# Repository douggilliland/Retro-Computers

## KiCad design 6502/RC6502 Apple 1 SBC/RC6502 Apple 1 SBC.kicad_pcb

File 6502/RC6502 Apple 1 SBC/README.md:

# RC6502 Apple 1 SBC

Did you ever wonder what the first computer created by Apple was like, and then checked what getting one might cost? Well, only a few were made and those that still exist probably would cost you more than my car! Steve Wozniak built what would later be called the Apple I computer in his garage, using only common over the counter components the result was an interesting computer that still holds the imagination of many computer geeks to this day. I don't own a garage so I was limited by whatever I could do from the confines of my kitchen table, the RC6502 was what I came up with and with the files freely available on GitHub you can too!

There are two versions of the RC6502, one has a card for every basic function such as CPU, RAM (redesigned version of also supports ROM), separate ROM as well as a serial card that replaces the traditional CRT and ASCII keyboard with an Arduino Nano. Doing it this way requires a backplane to connect everything together, this may be the version to build either because you want to study each of them in detail to figure out their secrets or simply because you want the option to easily replace them. The other one, this one actually, is the SBC-version (Single Board Computer) - this is the version to get if you want to learn a bit about the computer and enjoy building kits that are in a more compact form factor. It looks nice on shelf, or in a small drawer (if you don't get a vote on what belongs on display in your home). Most can be accomplished with the SBC version, so for your first build I recommend that you start with the SBC ([order](https://www.pcbway.com/project/shareproject/RC6502_Apple_1_SBC__revision_D_.html?inviteid=88707)) as well as a backplane ([order](https://www.pcbway.com/project/shareproject/RC6502_Apple_1_Replica__Backplane_module_revision_A_.html?inviteid=88707)) (so you can create and add features later).

Excited yet? Ofcourse you are, the next step is getting a PCB made and with the files available here you can have a company such as [PCBWay](https://www.pcbway.com/project/shareproject/RC6502_Apple_1_SBC__revision_D_.html?inviteid=88707) make a stack of them for around 5$, then have a look through the BOM (Bill Of Manufacturing) below to figure out what kind of components you'd need later to put it all together. Other than that you need basic tools such as a good soldering iron with a small-ish tip, lead-based solder with a resin core is recommended for beginners and then finally you'll need a basic EEPROM programmer (I use a cheap, but fantastic one called MiniPro TL866A).

The project uses only through-hole components that are easy for beginners, these have a set of pins or wires that are threaded through the holes of the PCB and then soldered on to the backside of the PCB. You can assemble it in the order of your own choosing as long as everything goes in the right place, but here are some hints to get started: do smaller parts such as the resistors first, then followed by the capacitors, IC sockets and then finally the larger components. By doing it this way, we're gradually going from the components closest to the board and successively moving onto taller components - this makes it easier to keep everything flush with the board. The components icons on the top of the PCB, what we hardware geeks usually refer to as the silkscreen, shows you which components goes where - take care that they are oriented the correct way, where it matters it'll be marked. Sockets will have a little indent marked on it similar to what you find on the PCB, for the electrolytic capacitors (round towers) you'll be able to match a stripe on one of the sides to the filled half of the symbol (this is the minus side).

Take it slow and steady, enjoy the feeling of building a computer by hand. Study the text on the backside of the PCB as you go along, it'll have some text on it describing what most of the components you are installing actually does! If afterwards you want to study everything in detail, you can do so by studying the schematic for the whole thing at your leasure. Having problems with it? Now, I'm afraid you no longer have the option to avoid the schematic, but happily most problems can be fixed by verifying each connection by using a cheap multimeter set to continuity mode. If you print the schematic, you can mark everything you've checked with a pen so you won't overlook anything - this is where you'll be learning the most! Sometimes the wrong things have been accidentally connected, usually by a stray splash of solder - these are quickly found using the same continuity check, systematically work through each of the ICs to see if pins next to each other have been connected without a corresponding link on the schematic. Don't feel bad that everything didn't work from the get go, that just means you got some extra opportunities to learn even more than expected!

The original computer had circuits for displaying data on a screen and reading input via a physical keyboard, but to keep things simple we are instead using an Arduino Nano to replace these parts - that way, you thanfully don't need to buy an antique keyboard or a scary CRT monitor in order to use it! You can communicate with the computer you built using a terminal emulator program such as PuTTy, SecureCRT or similar over the serial interface provided by the Arduino Nano. The Nano of course also need some software running on it, you'll find that in the form of an Arduino sketch called "[PIA Communicator](https://github.com/tebl/RC6502/tree/master/RC6502%20Serial%20IO/pia_communicator)", for more information see the details for the standalone [Serial IO](https://github.com/tebl/RC6502-Apple-1-Replica/tree/master/RC6502%20Serial%20IO)-module. 

The firmware that goes into the EEPROM hasn't been changed since Wozniak himself wrote it, but as long as you have the programmer handy you can easily flash it into place using the software that came with the programmer (MiniPro Programmer, if you bought the one I'm using). Today the [8 KB binary file](https://github.com/tebl/RC6502/tree/master/RC6502%20ROM/firmware) will seem really small, but even still it contains everything you'll need to get started and even a lot more. You've got a complete version of Basic environment in there, but since it's an Apple 1 the first thing you'll see is something called a computer monitor - WozMon! The monitor allows you to interact with the system by peeking and poking memory locations to your hearts content!

At this point you'll certainly have learned a lot, after all you've actually built an entire computer! Thankfully you had some modern tools available, but please take a moment to contemplate the genious needed to build this thing back in 1976! Still wanting more, why not try your hand at designing some extra modules to use with that backplane connector? Add a parallell port, replace the display portion with a proper LCD, or you could even go as far as adding a few pretty blinking lights - the possibilities are truly endless (so long as it's within 64K)!

## Errata
Revisions D and E of the SBC was missing a line powering the CPU, this is fixed by adding a piece of patch wire or simply a piece of resistor leftovers. Refer to the image below to see where it should be added, but leave some room so that it doesn't short to the pads now in the middle of the wire.

# Schematic
The supplied KiCad files should be sufficient as both a schematic and as a starting point for ordering PCBs (basically you could just zip the contents of the export folder and upload that on a fabrication site), the schematic is also available in [PDF-format](https://github.com/tebl/RC6502/raw/master/RC6502%20Apple%201%20SBC/export/RC6502%20Apple%201%20SBC.pdf) so that you can refer to it while troubleshooting. You could even print it out and hang it on your office wall, excellent conversation starter at any technology-oriented business worth working at!

# BOM
This is the part list as it stands now, most should be easy to get a hold of from your local electronic component shop though you might have to consider other sources for the older parts such as CPU, memory and PIA. Personally I bought most components with free shipping from China via AliExpress, prices will vary though you should be able to find most components in larger quantities than you'll ever need for the cost of a few cups of fancy coffee! You don't even need the newest and fastest components, after all it's going into a 70s-era computer so don't go overboard unless you absolutely want to (you can replace 74LS ICs with 74HCT or 74ALS if you want something newer). Most components have been produced by various manufacturers, these mostly do the same thing without any relevant differences though the choice of CPU and PIA could lead to incompatibilities so I've specified the ones I've had success with (probably also the cheapest ones available).

Some vendors will have the same ICs in different form factors, the ones you want will often be specified as being in the form of a DIP/PDIP package. Usually you'll want sockets for each of the ICs as well, a bag of assorted sockets should be easily available without setting you back more than a couple bucks. With the sockets in place, you don't need to dread having to remove an IC later, this leads to easier fault finding and you can easily "borrow"  them for other projects later! For the pin headers, both male and female - if you can't find the exact pin count, just buy the longer versions and snip off the parts you don't need. Electrolytic capacitors have a max voltage rating, the cheapest are 16V and should be more than enough - you can use higher rated components if you want to, but note that these might be slightly bigger thought you'll probably be able to fit in there anyway. Personally I prefer the look of the monolithic capacitors over the regular ceramic ones, but either is fine!

| Reference    | Item                                  | Count |
| ------------ | ------------------------------------- | ----- |
| PCB          | Fabricate yourself using Gerber files ([order](https://www.pcbway.com/project/shareproject/RC6502_Apple_1_SBC__revision_D_.html?inviteid=88707)) |     1 |
| U1           | 6502 CPU DIP-40, UM6502 or SY6502     |     1 |
| U2           | 62256 Static RAM DIP-28               |     1 |
| U3           | 74LS138 DIP                           |     1 |
| U4           | 28C64 or 28C256 DIP-28, EEPROM        |     1 |
| U5           | 74LS00 DIP                            |     1 |
| U6           | NE555 DIP                             |     1 |
| U7           | 74LS04 DIP                            |     1 |
| U8           | MC6821P PIA DIP-40                    |     1 |
| U9           | MCP23S17 DIP-28                       |     1 |
| X1           | 1.000Mhz TTL Oscillator, (DIP 14)     |     1 |
| R1,R6-R8,R10 | 3k3 (3300) ohm resistor               |     5 |
| R2           | 1M ohm resistor                       |     1 |
| R3           | 47k ohm resistor                      |     1 |
| R4           | 1k ohm resistor                       |     1 |
| R5           | 330 ohm resistor                      |     1 |
| R9           | 10k ohm resistor                      |     1 |
| D1           | 5mm LED diode, green or red color     |     1 |
| J1, J8       | Single row, 2p right angle connector  |     2 |
| J2           | 15p female pin headers                |     2 |
| J3           | Single row, 39p right angle connector |     1 |
| J4-J7        | Not needed, holes included with PCB   |     4 |
| J9, J10      | Single row, 3p right angle connector  |     2 |
| C1-C9, C11   | 100nF ceramic capacitor               |    10 |
| C10          | 10uF 16V electrolytic capacitor       |     1 |
| C12          | 10nF ceramic capacitor                |     1 |
| SW1          | Momentary push button                 |     1 |
|              | Jumpers for settings (CAP headers)    |     5 |
| Nano         | Arduino Nano v3.0 with USB cable      |     1 |

If you would like to have a copy of one or more modules, what you'll need to do is zip up the contents of the export directory for each module and give that to your favourite PCB fabrication plant. Personally I prefer to use [PCBWay](https://www.pcbway.com/setinvite.aspx?inviteid=88707), each module is only 5$ each and new accounts even get the first one free! Please use the supplied link when signing up to help me support this project, I'll get a small discount on future orders and hopefully I can afford to keep developing new and exciting modules. Some of the modules also have an order-link, using this you won't have to deal with the rather daunting PCB fabrication order forms so you know it'll work on the first order attempt!

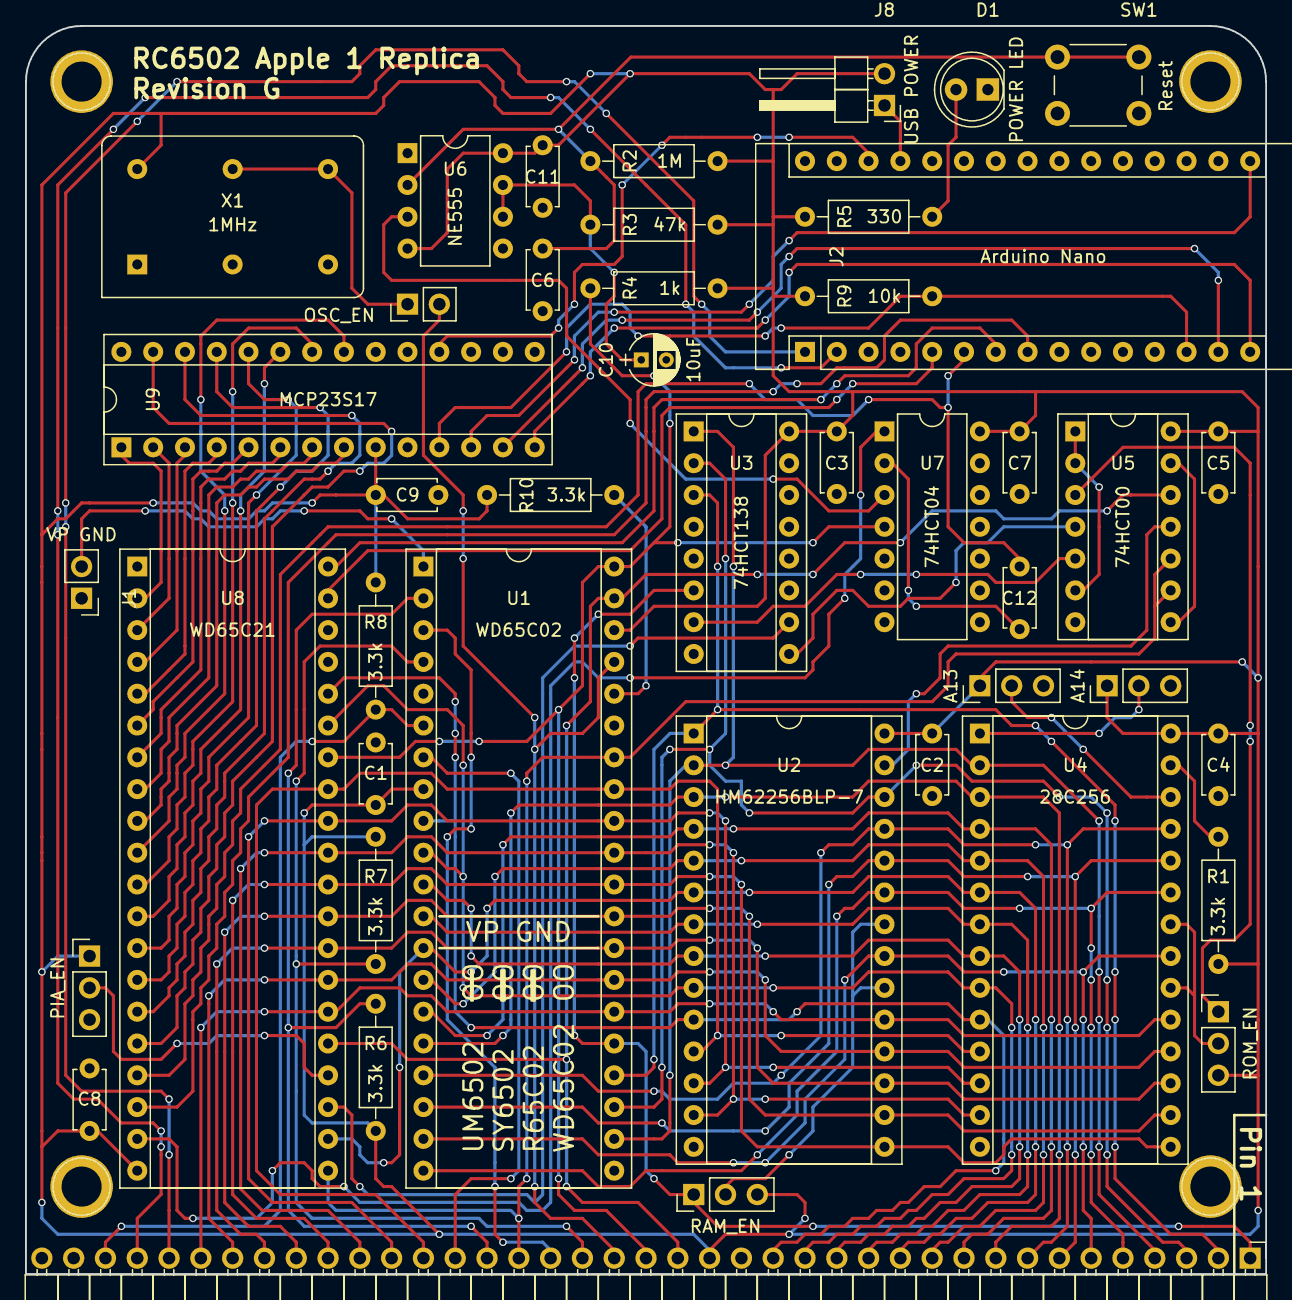
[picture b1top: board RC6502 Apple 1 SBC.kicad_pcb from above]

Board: 2 copper layers, 99.1 x 99.7 mm, 48 parts (0 on the bottom side), 84 nets.

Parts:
A13: A13 Select; Pin_Header_Straight_1x03_Pitch2.54mm
A14: A14 Select; Pin_Header_Straight_1x03_Pitch2.54mm
C1, C2, C3, C4, C5, C6, C7, C8, C9, C11: 100nF; C_Disc_D4.7mm_W2.5mm_P5.00mm
C10: 10uF; CP_Radial_D4.0mm_P2.00mm
C12: 10nF; C_Disc_D4.7mm_W2.5mm_P5.00mm
D1: Power; LED_D5.0mm
J1: VP GND; Pin_Header_Straight_1x02_Pitch2.54mm
J2: Arduino Nano; Arduino_Nano
J3: Backplane; Pin_Header_Angled_1x39_Pitch2.54mm
J4, J5, J6, J7: Hole; Mounting
J8: Power; Pin_Header_Angled_1x02_Pitch2.54mm
J9: ROM_EN; Pin_Header_Straight_1x03_Pitch2.54mm
J10: RAM_EN; Pin_Header_Straight_1x03_Pitch2.54mm
J11: PIA_EN; Pin_Header_Straight_1x03_Pitch2.54mm
JP1: OSC_EN; Pin_Header_Straight_1x02_Pitch2.54mm
R1, R6, R7, R8, R10: 3.3k; R_Axial_DIN0207_L6.3mm_D2.5mm_P10.16mm_Horizontal
R2: 1M; R_Axial_DIN0207_L6.3mm_D2.5mm_P10.16mm_Horizontal
R3: 47k; R_Axial_DIN0207_L6.3mm_D2.5mm_P10.16mm_Horizontal
R4: 1k; R_Axial_DIN0207_L6.3mm_D2.5mm_P10.16mm_Horizontal
R5: 330; R_Axial_DIN0207_L6.3mm_D2.5mm_P10.16mm_Horizontal
R9: 10k; R_Axial_DIN0207_L6.3mm_D2.5mm_P10.16mm_Horizontal
SW1: RESET; SW_PUSH_6mm
U1: WD65C02; DIP-40_W15.24mm_Socket
U2: HM62256BLP-7; DIP-28_W15.24mm_Socket
U3: 74HCT138; DIP-16_W7.62mm_Socket
U4: 28C256; DIP-28_W15.24mm_Socket
U5: 74HCT00; DIP-14_W7.62mm_Socket
U6: NE555; DIP-8_W7.62mm
U7: 74HCT04; DIP-14_W7.62mm
U8: WD65C21; DIP-40_W15.24mm_Socket
U9: MCP23S17; DIP-28_W7.62mm_Socket
X1: 1MHz; Oscillator_DIP-14

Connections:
A0: J3.16, U1.9, U2.10, U4.10, U8.36
A1: J3.15, U1.10, U2.9, U4.9, U8.35
A2: J3.14, U1.11, U2.8, U4.8
A3: J3.13, U1.12, U2.7, U4.7
A4: J3.12, U1.13, U2.6, U4.6, U8.22
A5: J3.11, U1.14, U2.5, U4.5
A6: J3.10, U1.15, U2.4, U4.4
A7: J3.9, U1.16, U2.3, U4.3
A8: J3.8, U1.17, U2.25, U4.25
A9: J3.7, U1.18, U2.24, U4.24
A10: J3.6, U1.19, U2.21, U4.21
A11: J3.5, U1.20, U2.23, U4.23
A12: J3.4, U1.22, U2.2, U3.1, U4.2
A13: J3.3, U1.23, U2.26, U3.2
A13_W: A13.2, U4.26
A14: J3.2, U1.24, U2.1, U3.3
A14_W: A14.2, U4.1
A15: J3.1, J10.1, U1.25, U3.6
CLOCK: J3.21, JP1.2, U1.37
CS_PIA: U3.10, U8.23
CS_ROM: J9.1, U5.3
D0: J3.27, U1.33, U2.11, U4.11, U8.33
D1: J3.28, U1.32, U2.12, U4.12, U8.32
D2: J3.29, U1.31, U2.13, U4.13, U8.31
D3: J3.30, U1.30, U2.15, U4.15, U8.30
D4: J3.31, U1.29, U2.16, U4.16, U8.29
D5: J3.32, U1.28, U2.17, U4.17, U8.28
D6: J3.33, U1.27, U2.18, U4.18, U8.27
D7: J3.34, U1.26, U2.19, U4.19, U8.26
GND: A13.3, A14.3, C1.2, C2.2, C3.2, C4.2, C5.2, C6.2, C7.2, C8.2, C9.2, C10.2, C11.2, D1.1, J1.1, J2.29, J3.17, J11.3, SW1.1, U1.21, U2.14, U3.4, U3.5, U3.8, U4.14, U5.7, U6.1, U7.5, U7.7, U7.9, U7.11, U7.13, U8.1, U9.10, U9.15, U9.16, U9.17, X1.7
IRQ: J3.22, R7.1, U1.4
KBD_D0: U8.2, U9.1
KBD_D1: U8.3, U9.2
KBD_D2: U8.4, U9.3
KBD_D3: U8.5, U9.4
KBD_D4: U8.6, U9.5
KBD_D5: U8.7, U9.6
KBD_D6: U8.8, U9.7
KBD_D7: U8.9, U9.8
KBD_READY: J2.5, U8.39
KBD_STROBE: J2.7, U8.40
NMI: J3.37, R8.1, U1.6
unnamed: C6.1, R2.2, SW1.2, U6.2
unnamed: C10.1, R3.2, U6.6, U6.7
unnamed: C12.2, U7.2
unnamed: D1.2, R5.2
unnamed: J1.2, U1.1
unnamed: J2.13, R9.2, U9.11
unnamed: J2.14, U9.13
unnamed: J2.15, U9.14
unnamed: J2.16, U9.12
unnamed: J2.27, J8.1
unnamed: J9.2, U4.20, U4.22
unnamed: J10.2, U2.20, U2.22
unnamed: J11.2, U8.24
unnamed: JP1.1, X1.8
unnamed: R1.1, U4.27
unnamed: R10.1, U1.36
unnamed: U2.27, U5.11
unnamed: U3.7, U5.5
unnamed: U3.9, U5.4
unnamed: U5.1, U5.2, U5.6
unnamed: U5.8, U5.13
unnamed: U6.3, U7.3
unnamed: U7.1, U8.19
OUT_D0: U8.10, U9.21
OUT_D1: U8.11, U9.22
OUT_D2: U8.12, U9.23
OUT_D3: U8.13, U9.24
OUT_D4: U8.14, U9.25
OUT_D5: U8.15, U9.26
OUT_D6: U8.16, U9.27
OUT_DA: C12.1, J2.6, U8.17
OUT_RDA: J2.8, U8.18
PHI1: J3.23, U1.3
PHI2: J3.19, U1.39, U5.12, U8.25
P_RESET: J2.28, U9.18
RDY: J3.25, R6.1, U1.2
RESET: J3.20, R4.1, U1.40, U7.4, U8.34
RW: J3.24, U1.34, U5.9, U5.10, U8.21
RX: J2.2, J3.36
SYNC: J3.26, U1.7
TX: J2.1, J3.35
VCC: A13.1, A14.1, C1.1, C2.1, C3.1, C4.1, C5.1, C7.1, C8.1, C9.1, C11.1, J3.18, J8.2, J9.3, J10.3, J11.1, R1.2, R2.1, R3.1, R4.2, R5.1, R6.2, R7.2, R8.2, R9.1, R10.2, U1.8, U1.38, U2.28, U3.16, U4.28, U5.14, U6.4, U6.8, U7.14, U8.20, U9.9, X1.14

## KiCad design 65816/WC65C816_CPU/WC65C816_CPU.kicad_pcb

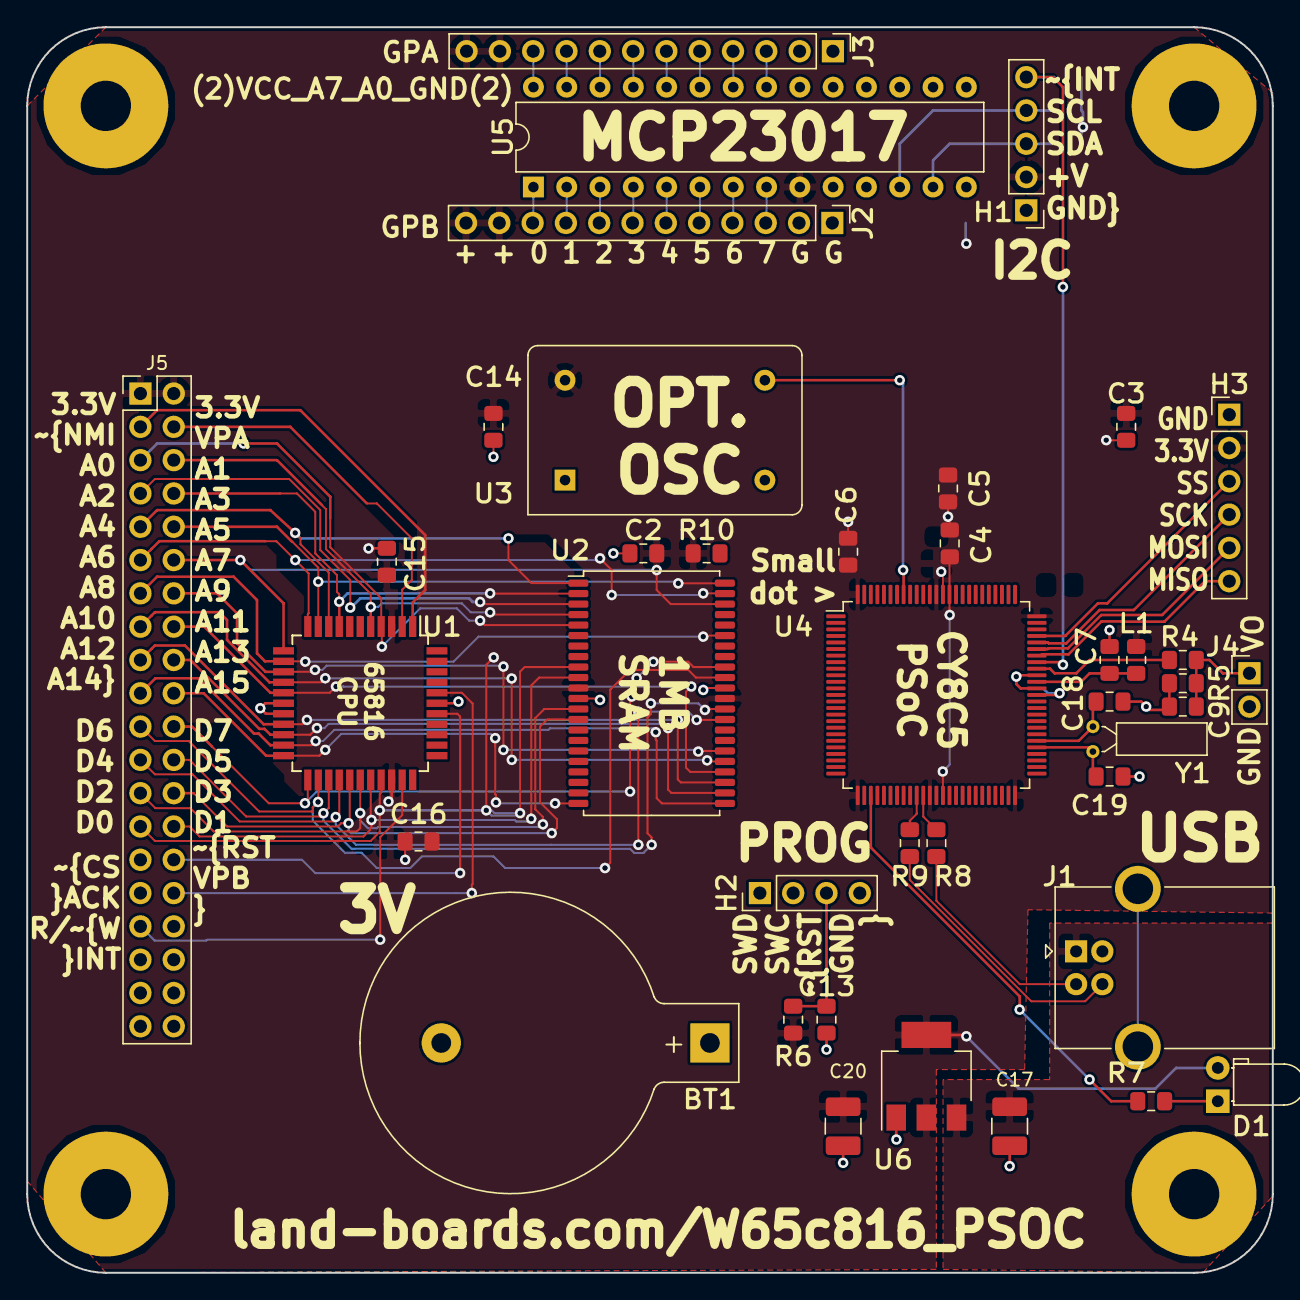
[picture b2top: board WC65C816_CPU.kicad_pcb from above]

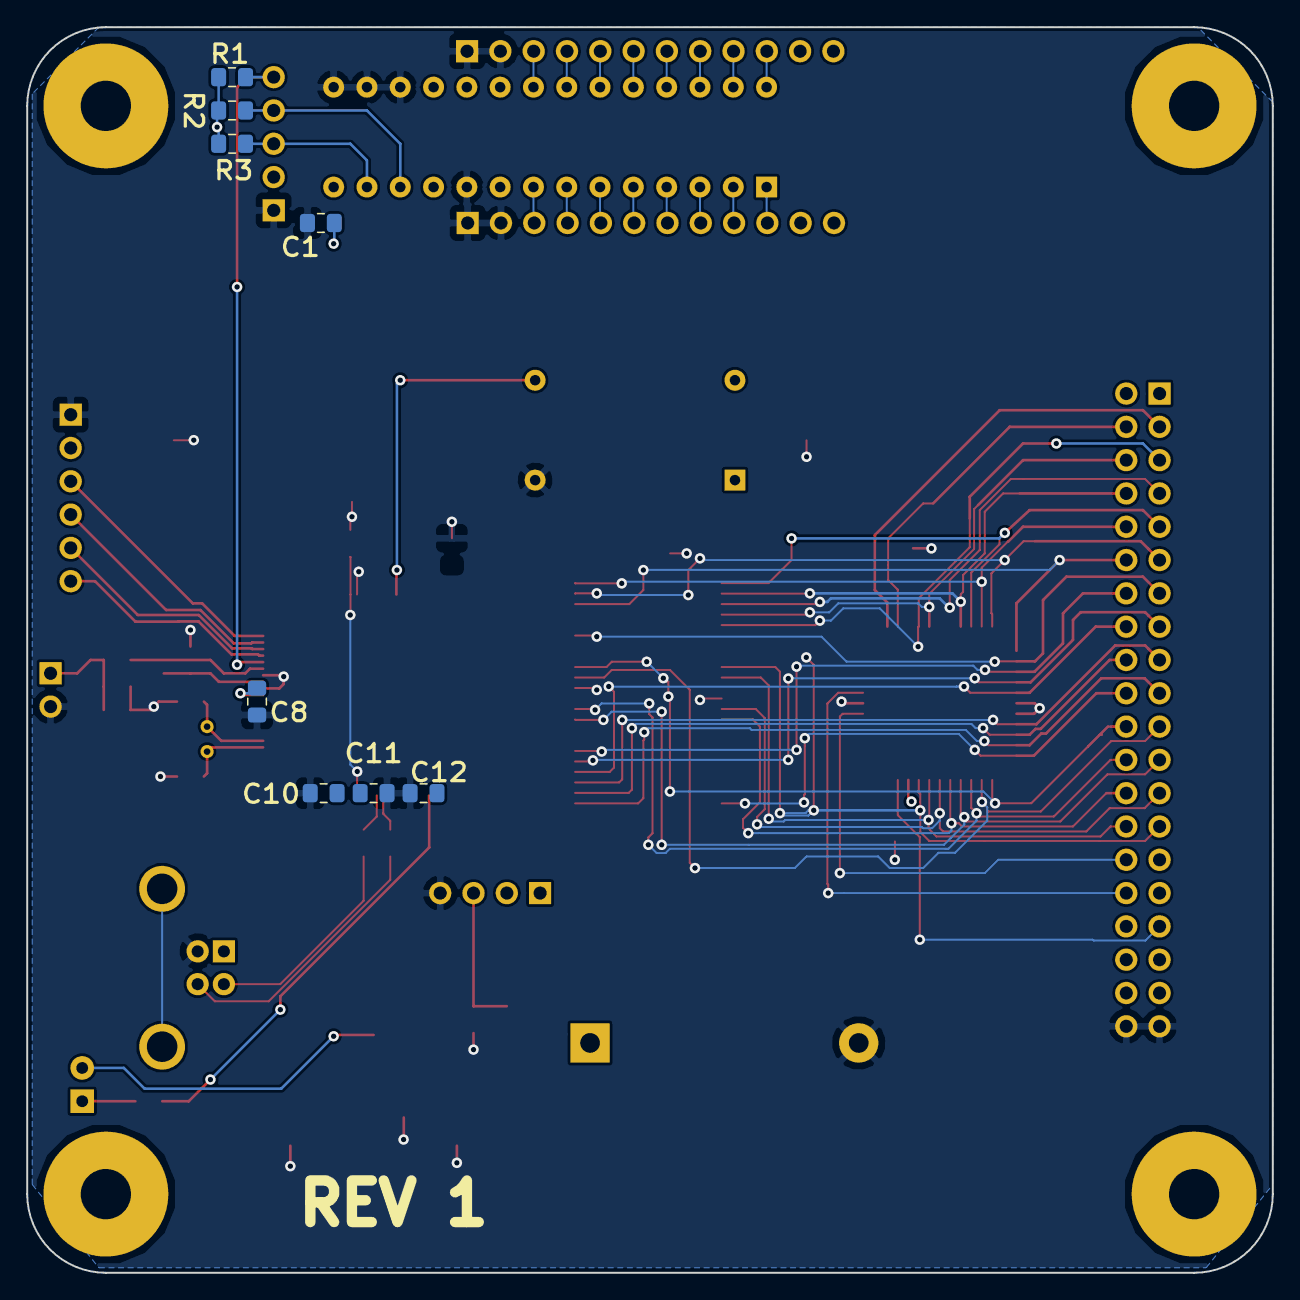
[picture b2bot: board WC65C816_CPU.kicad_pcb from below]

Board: 2 copper layers, 95.0 x 95.0 mm, 52 parts (8 on the bottom side), 91 nets.

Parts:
BT1: Battery_Cell; BatteryHolder_Keystone_103_1x20mm
C1, C2, C3, C5, C6, C11, C12, C13, C14, C15, C16: 0.1uF; C_0805_2012Metric_Pad1.15x1.40mm_HandSolder
C4, C7, C8, C10: 1uF; C_0805_2012Metric_Pad1.15x1.40mm_HandSolder
C9: 0.001uF; C_0805_2012Metric_Pad1.15x1.40mm_HandSolder
C17, C20: 10uF; C_1210_3225Metric_Pad1.42x2.65mm_HandSolder
C18, C19: 8pF; C_0805_2012Metric_Pad1.15x1.40mm_HandSolder
D1: LED; LED_D3.0mm_Horizontal_O1.27mm_Z2.0mm
H1: Conn_01x05; PinHeader_1x05_P2.54mm_Vertical
H2: Conn_01x04; PinHeader_1x04_P2.54mm_Vertical
H3: Conn_01x06; PinHeader_1x06_P2.54mm_Vertical
J1: USB_B; USB_B_OST_USB-B1HSxx_Horizontal
J2, J3: Conn_01x12; PinHeader_1x12_P2.54mm_Vertical
J4: Conn_01x02; PinHeader_1x02_P2.54mm_Vertical
J5: Conn_02x20_Odd_Even; PinHeader_2x20_P2.54mm_Vertical
L1: ChipInd; L_0805_2012Metric_Pad1.15x1.40mm_HandSolder
MTG1, MTG2, MTG3, MTG4: MTG_HOLE; MTG-6-32
R1, R2, R3, R4, R10: 2.2K; R_0805_2012Metric_Pad1.15x1.40mm_HandSolder
R5: 100; R_0805_2012Metric_Pad1.15x1.40mm_HandSolder
R6: 3.9K; R_0805_2012Metric_Pad1.15x1.40mm_HandSolder
R7: 330; R_0805_2012Metric_Pad1.15x1.40mm_HandSolder
R8, R9: 22; R_0805_2012Metric_Pad1.15x1.40mm_HandSolder
U1: W65C816S; LQFP-44_10x10mm_P0.8mm
U2: IS62WV10248EBLL-45TLI; TSOP-II-44_10.16x18.41mm_P0.8mm
U3: 4.9152 MHz; Oscillator_DIP-14
U4: CY8C5267AXI-LP051; TQFP-100_14x14mm_P0.5mm
U5: MCP23017_SP; DIP-28_W7.62mm
U6: AP1117; SOT-223
Y1: 32.768KHz; Crystal_C26-LF_D2.1mm_L6.5mm_Horizontal

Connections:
+3V3: C1.2, C2.2, C3.2, C5.2, C6.2, C11.2, C12.2, C14.2, C15.2, C16.2, C20.2, D1.2, H1.2, H3.2, J2.11, J2.12, J3.11, J3.12, J5.1, J5.2, L1.2, R1.1, R2.1, R3.1, R6.1, R10.2, U1.3, U1.31, U2.11, U2.33, U3.14, U4.26, U4.37, U4.50, U4.75, U4.88, U4.100, U5.9, U6.2, U6.4
+5V: C17.2, J1.1, U6.3
/BE: U1.34, U4.43
/CPUA0: J5.5, U1.4, U2.5, U4.89
/CPUA1: J5.6, U1.5, U2.4, U4.90
/CPUA2: J5.7, U1.7, U2.3, U4.91
/CPUA3: J5.8, U1.8, U2.2, U4.92
/CPUA4: J5.9, U1.9, U2.1, U4.95
/CPUA5: J5.10, U1.10, U2.44, U4.96
/CPUA6: J5.11, U1.11, U2.43, U4.97
/CPUA7: J5.12, U1.12, U2.42, U4.98
/CPUA8: J5.13, U1.13, U2.39, U4.2
/CPUA9: J5.14, U1.14, U2.28, U4.3
/CPUA10: J5.15, U1.15, U2.27, U4.80
/CPUA11: J5.16, U1.16, U2.26, U4.81
/CPUA12: J5.17, U1.19, U2.25, U4.82
/CPUA13: J5.18, U1.20, U2.24, U4.83
/CPUA14: J5.19, U1.21, U2.23, U4.84
/CPUA15: J5.20, U1.22, U2.22, U4.85
/CPUD0: J5.27, U1.30, U2.9, U4.16
/CPUD1: J5.28, U1.29, U2.10, U4.17
/CPUD2: J5.25, U1.28, U2.13, U4.18
/CPUD3: J5.26, U1.27, U2.14, U4.19
/CPUD4: J5.23, U1.26, U2.31, U4.31
/CPUD5: J5.24, U1.25, U2.32, U4.32
/CPUD6: J5.21, U1.24, U2.35, U4.33
/CPUD7: J5.22, U1.23, U2.36, U4.34
/DAC_OUT: R4.2, U4.67
/E: U1.33, U4.52
/GPA0: J3.3, U5.21
/GPA1: J3.4, U5.22
/GPA2: J3.5, U5.23
/GPA3: J3.6, U5.24
/GPA4: J3.7, U5.25
/GPA5: J3.8, U5.26
/GPA6: J3.9, U5.27
/GPA7: J3.10, U5.28
/GPB0: J2.10, U5.1
/GPB1: J2.9, U5.2
/GPB2: J2.8, U5.3
/GPB3: J2.7, U5.4
/GPB4: J2.6, U5.5
/GPB5: J2.5, U5.6
/GPB6: J2.4, U5.7
/GPB7: J2.3, U5.8
/LED: R7.2, U4.28
/MX: U1.36, U4.51
/R/~W: J5.33, U1.32, U4.42
/RCS: R10.1, U2.40
/RDY: U1.41, U4.45
/SCL: H1.4, R2.2, U4.4, U5.12
/SDA: H1.3, R3.2, U4.5, U5.13
/SPIMISO: H3.6, U4.69
/SPIMOSI: H3.5, U4.70
/SPISCK: H3.4, U4.71
/SPISS: H3.3, U4.72
/SRAMA16: U2.21, U4.6
/SRAMA17: U2.20, U4.7
/SRAMA18: U2.19, U4.8
/SRAMA19: U2.18, U4.9
/SWC: H2.2, U4.21
/SWD: H2.1, U4.20
/USB-DM: J1.2, R8.1
/USB-DP: J1.3, R9.1
/VDA: U1.37, U4.49
/VPA: J5.4, U1.2, U4.79
/VPB: J5.32, U1.40, U4.99
/~ABTB: U1.42, U4.46
/~I2CINT: H1.5, R1.2, U4.68
/~IOACK: J5.31, U4.25
/~IOCS: J5.29, U4.27
/~IOINT: J5.35, U4.24
/~IRQ: U1.43, U4.47
/~MEMWR: U2.17, U4.73
/~ML: U1.44, U4.44
/~NMI: J5.3, U1.1, U4.78
/~RESB: J5.30, U1.38, U4.23, U5.18
/~SRAMCS: U2.6, U4.74
GND: BT1.2, C1.1, C2.1, C3.1, C4.2, C5.1, C6.1, C7.2, C8.2, C9.1, C10.2, C11.1, C12.1, C13.2, C14.1, C15.1, C16.1, C17.1, C18.1, C19.1, C20.1, H1.1, H2.4, H3.1, J1.4, J2.1, J2.2, J3.1, J3.2, J4.2, J5.39, J5.40, R5.1, U1.17, U1.18, U1.39, U2.12, U2.34, U3.7, U4.10, U4.12, U4.14, U4.38, U4.64, U4.66, U4.87, U5.10, U5.15, U5.16, U5.17, U6.1
unnamed: BT1.1, U4.13
unnamed: C7.1, L1.1, U4.65
unnamed: C8.1, U4.63
unnamed: C9.2, J4.1, R4.1, R5.2
unnamed: C4.1, C10.1, U4.39, U4.86
unnamed: C13.1, H2.3, R6.2, U4.15
unnamed: C18.2, U4.56, Y1.2
unnamed: C19.2, U4.55, Y1.1
unnamed: D1.1, R7.1
unnamed: R8.2, U4.36
unnamed: R9.2, U4.35
unnamed: U3.8, U4.93

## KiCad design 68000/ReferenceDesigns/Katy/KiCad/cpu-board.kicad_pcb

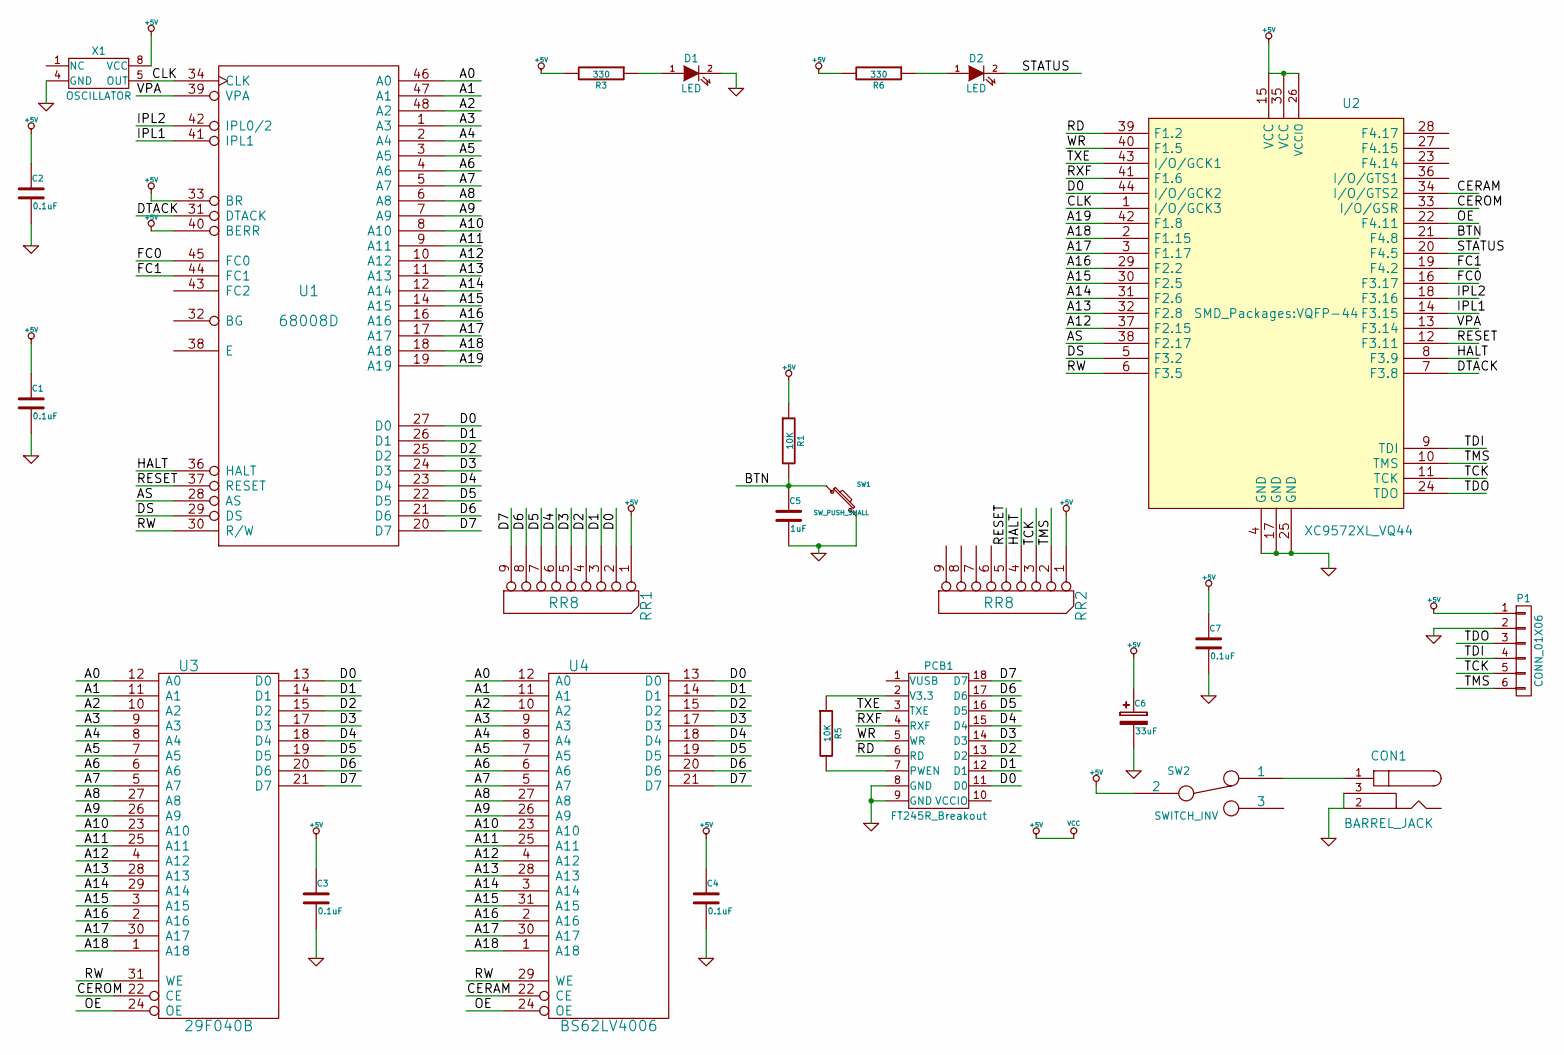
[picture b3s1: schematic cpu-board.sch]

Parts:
C1, C2, C3, C4, C7: 0.1uF; C1
C5: 1uF; C1
C6: 33uF; C1
CON1: BARREL_JACK; BMOW_BARREL_JACK
D1, D2: LED; LED-5MM
P1: CONN_01X06; Pin_Header_Straight_1x06
PCB1: FT245R_Breakout; FT245_Breakout
R1, R5: 10K; R3-5
R3, R6: 330; R3-5
RR1, RR2: RR8; r_pack8
SW1: SW_PUSH_SMALL
SW2: SWITCH_INV; MICROSWITCH_SPST
U1: 68008D; DIP-48__600_ELL
U2: XC9572XL_VQ44; VQFP-44
U3: 29F040B; DIP-32__600_ELL
U4: BS62LV4006; DIP-32__600_ELL
X1: OSCILLATOR; DIP-8__300_ELL

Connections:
+5V: C1.1, C2.1, C3.1, C4.1, C6.1, C7.1, P1.1, R1.1, R3.2, R6.2, RR1.1 (COM), RR2.1 (COM), SW2.2, U1.13 (VCC), U1.33 (BR), U1.40 (BERR), U2.15 (VCC), U2.26 (VCCIO), U2.35 (VCC), U3.32 (VCC), U4.32 (VCC), X1.8 (VCC)
/A0: U1.46 (A0), U3.12 (A0), U4.12 (A0)
/A1: U1.47 (A1), U3.11 (A1), U4.11 (A1)
/A2: U1.48 (A2), U3.10 (A2), U4.10 (A2)
/A3: U1.1 (A3), U3.9 (A3), U4.9 (A3)
/A4: U1.2 (A4), U3.8 (A4), U4.8 (A4)
/A5: U1.3 (A5), U3.7 (A5), U4.7 (A5)
/A6: U1.4 (A6), U3.6 (A6), U4.6 (A6)
/A7: U1.5 (A7), U3.5 (A7), U4.5 (A7)
/A8: U1.6 (A8), U3.27 (A8), U4.27 (A8)
/A9: U1.7 (A9), U3.26 (A9), U4.26 (A9)
/A10: U1.8 (A10), U3.23 (A10), U4.23 (A10)
/A11: U1.9 (A11), U3.25 (A11), U4.25 (A11)
/A12: U1.10 (A12), U2.37 (F2.15), U3.4 (A12), U4.4 (A12)
/A13: U1.11 (A13), U2.32 (F2.8), U3.28 (A13), U4.28 (A13)
/A14: U1.12 (A14), U2.31 (F2.6), U3.29 (A14), U4.3 (A14)
/A15: U1.14 (A15), U2.30 (F2.5), U3.3 (A15), U4.31 (A15)
/A16: U1.16 (A16), U2.29 (F2.2), U3.2 (A16), U4.2 (A16)
/A17: U1.17 (A17), U2.3 (F1.17), U3.30 (A17), U4.30 (A17)
/A18: U1.18 (A18), U2.2 (F1.15), U3.1 (A18), U4.1 (A18)
/A19: U1.19 (A19), U2.42 (F1.8)
/AS: U1.28 (AS), U2.38 (F2.17)
/BTN: C5.1, R1.2, SW1.1, U2.21 (F4.8)
/CERAM: U2.34 (I/O/GTS2), U4.22 (CE)
/CEROM: U2.33 (I/O/GSR), U3.22 (CE)
/CLK: U1.34 (CLK), U2.1 (I/O/GCK3), X1.5 (OUT)
/D0: PCB1.11 (D0), RR1.2, U1.27 (D0), U2.44 (I/O/GCK2), U3.13 (D0), U4.13 (D0)
/D1: PCB1.12 (D1), RR1.3, U1.26 (D1), U3.14 (D1), U4.14 (D1)
/D2: PCB1.13 (D2), RR1.4, U1.25 (D2), U3.15 (D2), U4.15 (D2)
/D3: PCB1.14 (D3), RR1.5, U1.24 (D3), U3.17 (D3), U4.17 (D3)
/D4: PCB1.15 (D4), RR1.6, U1.23 (D4), U3.18 (D4), U4.18 (D4)
/D5: PCB1.16 (D5), RR1.7, U1.22 (D5), U3.19 (D5), U4.19 (D5)
/D6: PCB1.17 (D6), RR1.8, U1.21 (D6), U3.20 (D6), U4.20 (D6)
/D7: PCB1.18 (D7), RR1.9, U1.20 (D7), U3.21 (D7), U4.21 (D7)
/DS: U1.29 (DS), U2.5 (F3.2)
/DTACK: U1.31 (DTACK), U2.7 (F3.8)
/FC0: U1.45 (FC0), U2.16 (F3.17)
/FC1: U1.44 (FC1), U2.19 (F4.2)
/HALT: RR2.4, U1.36 (HALT), U2.8 (F3.9)
/IPL1: U1.41 (IPL1), U2.14 (F3.15)
/IPL2: U1.42 (IPL0/2), U2.18 (F3.16)
/OE: U2.22 (F4.11), U3.24 (OE), U4.24 (OE)
/RD: PCB1.6 (RD), U2.39 (F1.2)
/RESET: RR2.5, U1.37 (RESET), U2.12 (F3.11)
/RW: U1.30 (R/W), U2.6 (F3.5), U3.31 (WE), U4.29 (WE)
/RXF: PCB1.4 (RXF), U2.41 (F1.6)
/STATUS: D2.2 (K), U2.20 (F4.5)
/TCK: P1.5, RR2.3, U2.11 (TCK)
/TDI: P1.4, U2.9 (TDI)
/TDO: P1.3, U2.24 (TDO)
/TMS: P1.6, RR2.2, U2.10 (TMS)
/TXE: PCB1.3 (TXE), U2.43 (I/O/GCK1)
/VPA: U1.39 (VPA), U2.13 (F3.14)
/WR: PCB1.5 (WR), U2.40 (F1.5)
GND: C1.2, C2.2, C3.2, C4.2, C5.2, C6.2, C7.2, CON1.2, CON1.3, D1.2 (K), P1.2, PCB1.8 (GND), PCB1.9 (GND), SW1.2, U1.15 (GND), U1.35 (GND), U2.4 (GND), U2.17 (GND), U2.25 (GND), U3.16 (GND), U4.16 (GND), X1.4 (GND)
unnamed: CON1.1, SW2.1
unnamed: D1.1 (A), R3.1
unnamed: D2.1 (A), R6.1
unnamed: PCB1.2 (V3.3), R5.1
unnamed: PCB1.7 (PWEN), R5.2

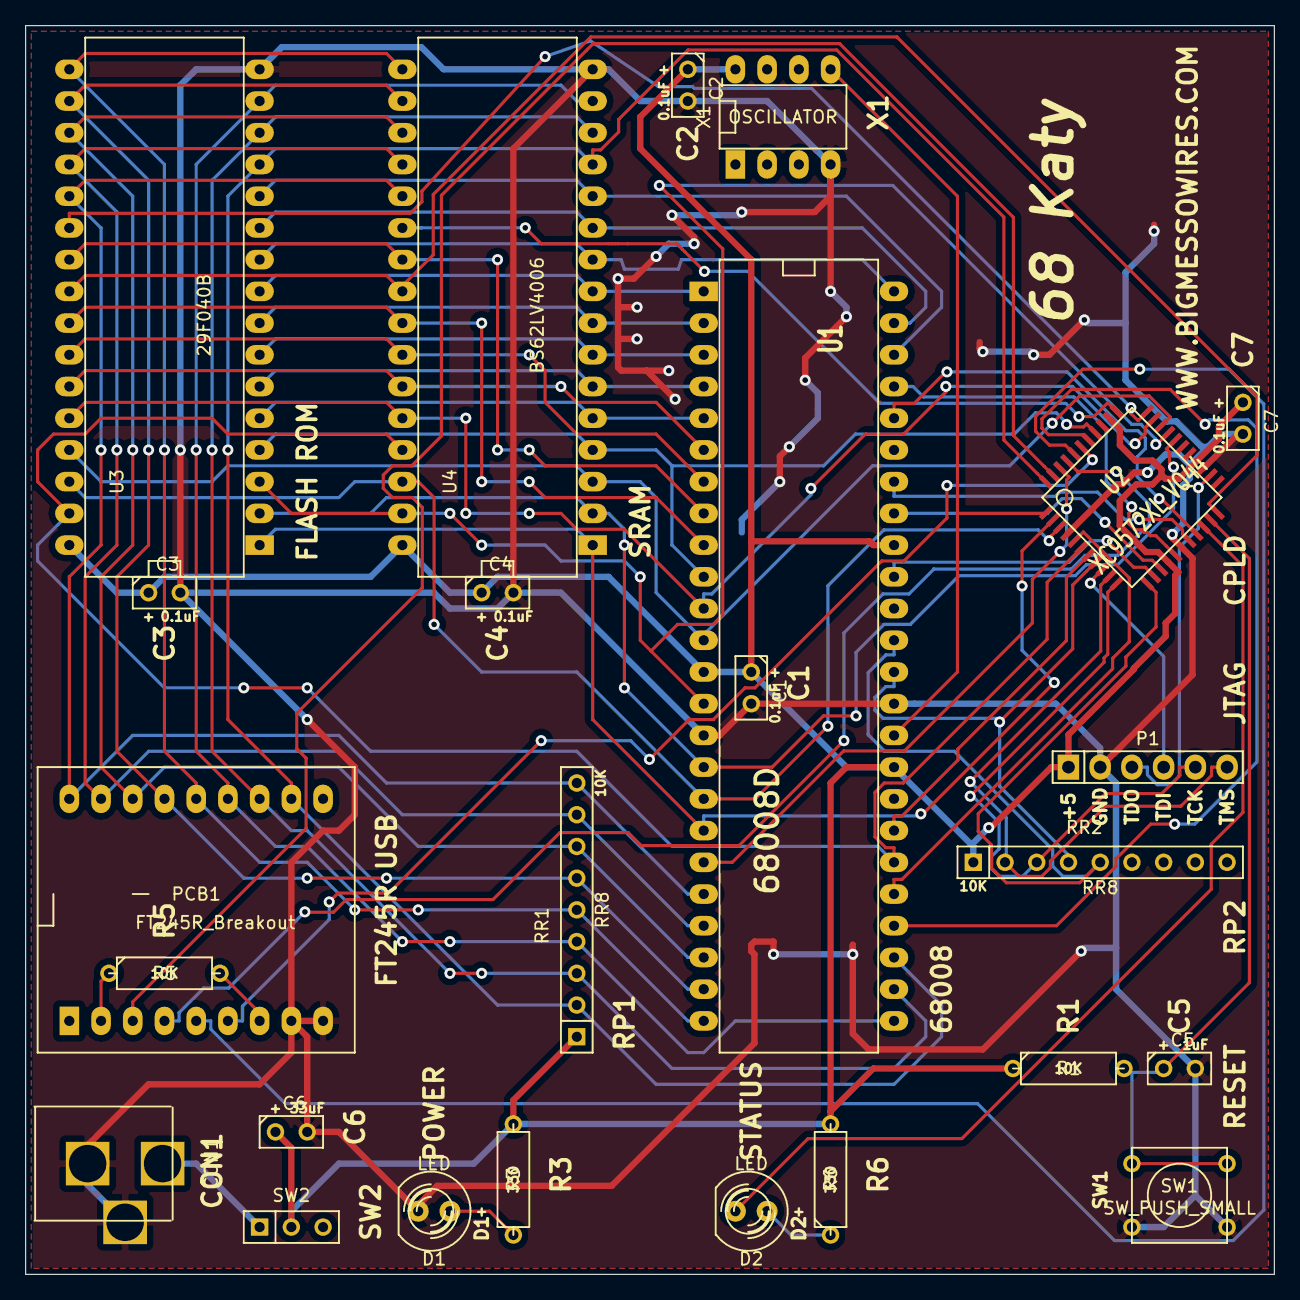
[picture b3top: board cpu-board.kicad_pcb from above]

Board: 2 copper layers, 100.0 x 100.0 mm, 25 parts (0 on the bottom side), 60 nets.
